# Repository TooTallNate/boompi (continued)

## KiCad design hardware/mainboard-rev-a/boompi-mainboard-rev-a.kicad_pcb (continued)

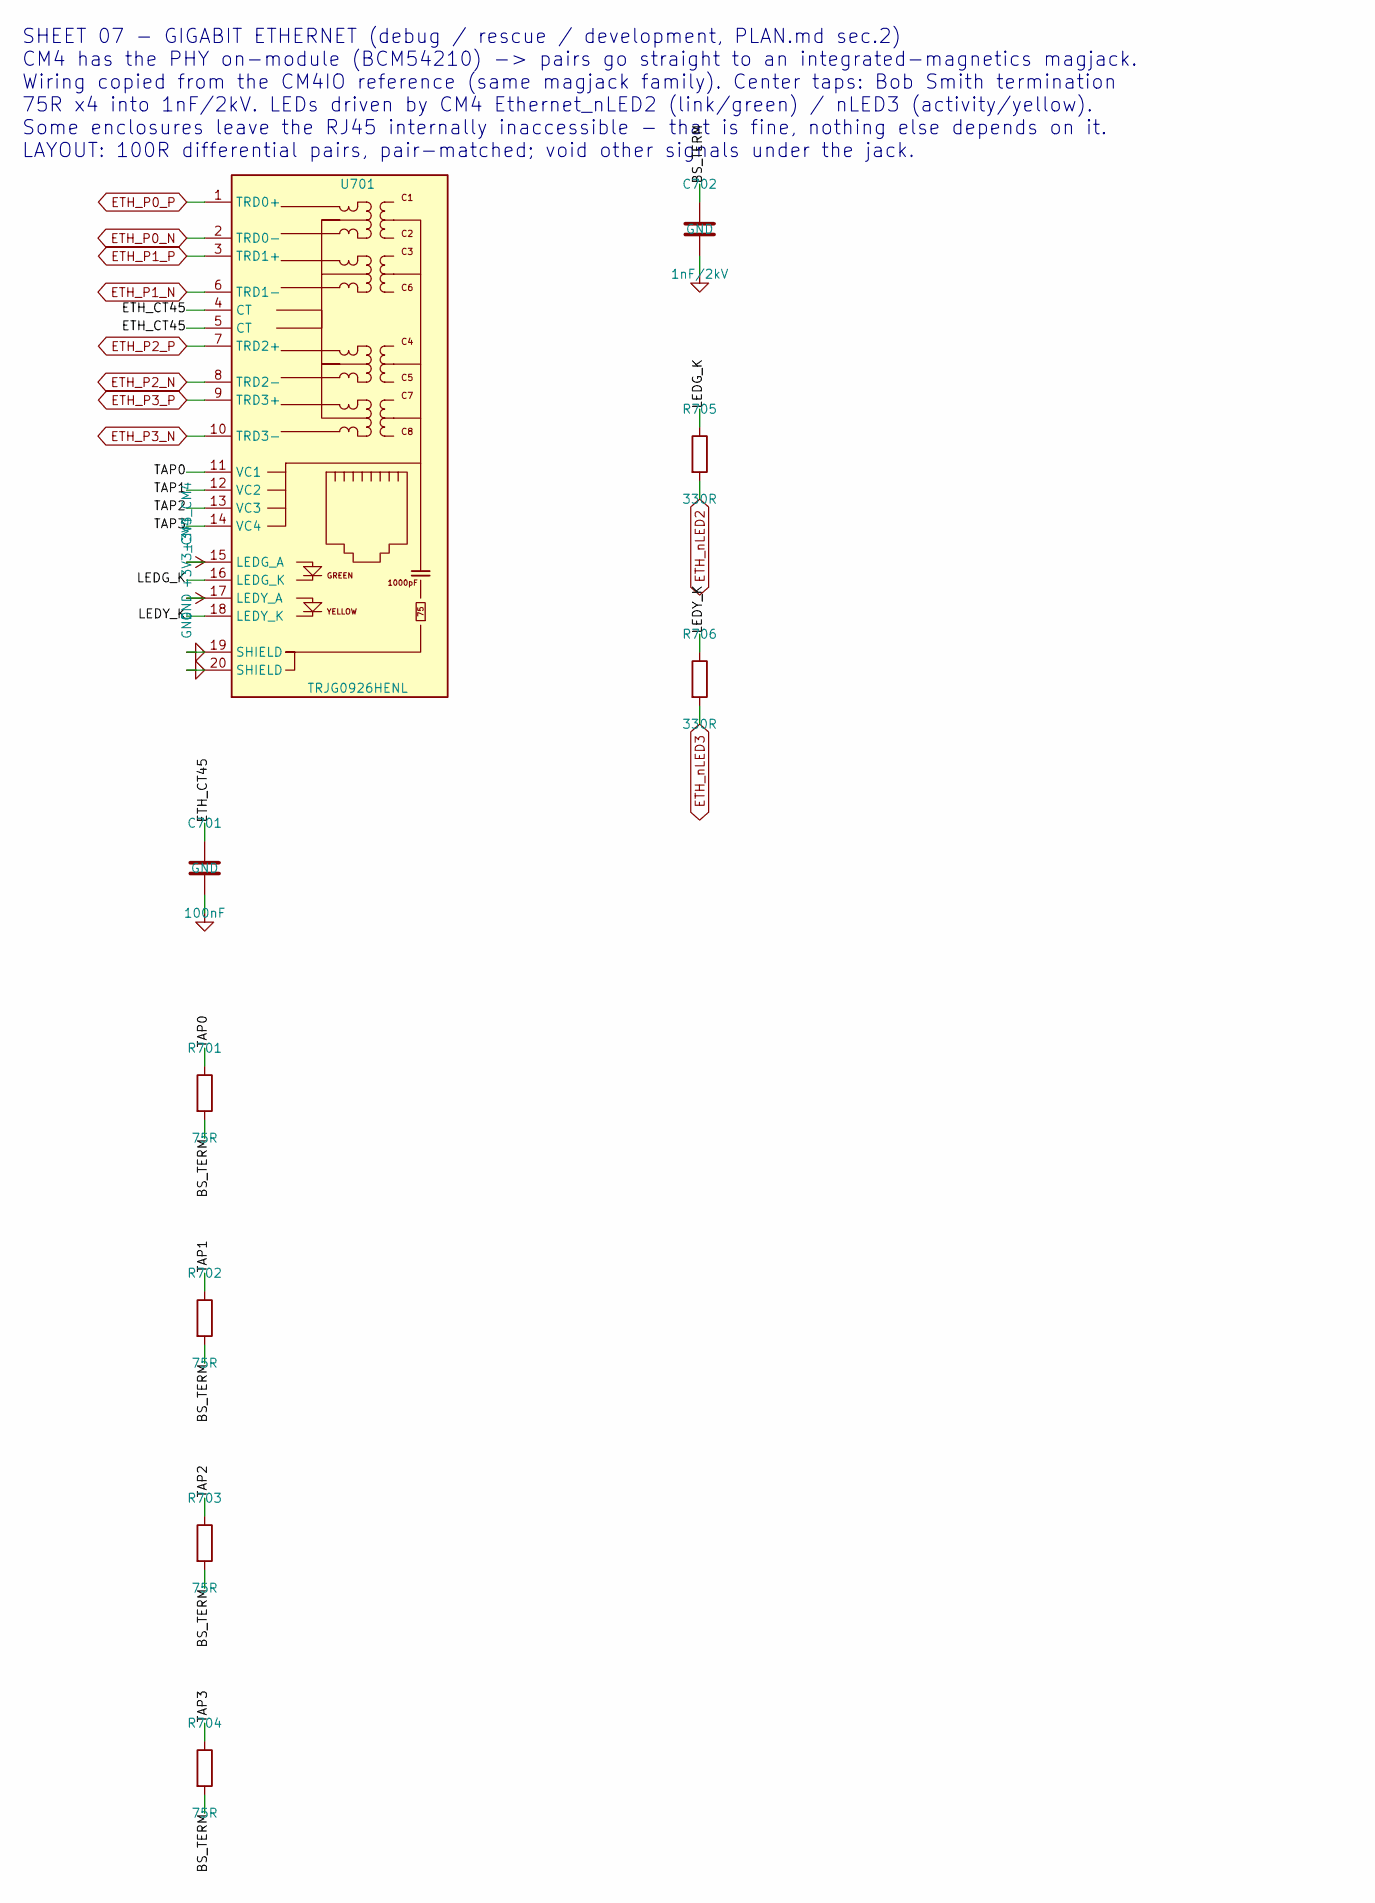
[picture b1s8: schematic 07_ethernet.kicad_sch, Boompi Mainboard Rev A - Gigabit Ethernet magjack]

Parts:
C701: 100nF; C_0603_1608Metric
C702: 1nF/2kV; C_1812_4532Metric
R701, R702, R703, R704: 75R; R_0603_1608Metric
R705, R706: 330R; R_0603_1608Metric
U701: TRJG0926HENL; MPN TRP TRJG0926HENL

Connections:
+3V3_CM4: U701.15 (LEDG_A), U701.17 (LEDY_A); also elsewhere on the board
/07_ETHERNET/BS_TERM: C702.1, R701.2, R702.2, R703.2, R704.2
/07_ETHERNET/ETH_CT45: C701.1, U701.4 (CT), U701.5 (CT)
/07_ETHERNET/LEDG_K: R705.1, U701.16 (LEDG_K)
/07_ETHERNET/LEDY_K: R706.1, U701.18 (LEDY_K)
/07_ETHERNET/TAP0: R701.1, U701.11 (VC1)
/07_ETHERNET/TAP1: R702.1, U701.12 (VC2)
/07_ETHERNET/TAP2: R703.1, U701.13 (VC3)
/07_ETHERNET/TAP3: R704.1, U701.14 (VC4)
ETH_P0_N: U701.2 (TRD0-); also elsewhere on the board
ETH_P0_P: U701.1 (TRD0+); also elsewhere on the board
ETH_P1_N: U701.6 (TRD1-); also elsewhere on the board
ETH_P1_P: U701.3 (TRD1+); also elsewhere on the board
ETH_P2_N: U701.8 (TRD2-); also elsewhere on the board
ETH_P2_P: U701.7 (TRD2+); also elsewhere on the board
ETH_P3_N: U701.10 (TRD3-); also elsewhere on the board
ETH_P3_P: U701.9 (TRD3+); also elsewhere on the board
ETH_nLED2: R705.2; also elsewhere on the board
ETH_nLED3: R706.2; also elsewhere on the board
GND: C701.2, C702.2, U701.19 (SHIELD), U701.20 (SHIELD); also elsewhere on the board

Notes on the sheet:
SHEET 07 - GIGABIT ETHERNET (debug / rescue / development, PLAN.md sec.2) CM4 has the PHY on-module (BCM54210) -> pairs go straight to an integrated-magnetics magjack. Wiring copied from the CM4IO reference (same magjack family). Center taps: Bob Smith termination 75R x4 into 1nF/2kV. LEDs driven b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

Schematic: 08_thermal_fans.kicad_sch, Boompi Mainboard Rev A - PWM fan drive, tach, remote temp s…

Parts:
J801: FAN1; PinHeader_1x04_P2.54mm_Vertical; MPN Molex 47053-1000 (4-pin fan)
J802: FAN2; PinHeader_1x04_P2.54mm_Vertical; MPN Molex 47053-1000 (4-pin fan)
J803: FAN3; PinHeader_1x04_P2.54mm_Vertical; MPN Molex 47053-1000 (4-pin fan); not fitted
J804: REMOTE_TEMP; JST_PH_B4B-PH-K_1x04_P2.00mm_Vertical; MPN JST B4B-PH-K-S
Q801, Q802: 2N7002; SOT-23
Q803: 2N7002; SOT-23; not fitted
R811, R821: 100R; R_0603_1608Metric
R812, R822: 100k; R_0603_1608Metric
R813, R814, R823, R824: 10k; R_0603_1608Metric
R815, R825: 1k; R_0603_1608Metric
R831: 100R; R_0603_1608Metric; not fitted
R832: 100k; R_0603_1608Metric; not fitted
R833, R834: 10k; R_0603_1608Metric; not fitted
R835: 1k; R_0603_1608Metric; not fitted

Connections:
+3V3_AON: J804.1, R814.1, R824.1, R834.1; also elsewhere on the board
+5V_MAIN: J801.2, J802.2, J803.2, R813.1, R823.1, R833.1; also elsewhere on the board
/08_THERMAL_FANS/FAN1_G: Q801.1 (G), R811.2, R812.1
/08_THERMAL_FANS/FAN1_PWM: J801.4, Q801.3 (D), R813.2
/08_THERMAL_FANS/FAN1_T_RAW: J801.3, R814.2, R815.1
/08_THERMAL_FANS/FAN2_G: Q802.1 (G), R821.2, R822.1
/08_THERMAL_FANS/FAN2_PWM: J802.4, Q802.3 (D), R823.2
/08_THERMAL_FANS/FAN2_T_RAW: J802.3, R824.2, R825.1
/08_THERMAL_FANS/FAN3_G: Q803.1 (G), R831.2, R832.1
/08_THERMAL_FANS/FAN3_PWM: J803.4, Q803.3 (D), R833.2
/08_THERMAL_FANS/FAN3_T_RAW: J803.3, R834.2, R835.1
FAN1_PWM_CTL: R811.1; also elsewhere on the board
FAN1_TACH: R815.2; also elsewhere on the board
FAN2_PWM_CTL: R821.1; also elsewhere on the board
FAN2_TACH: R825.2; also elsewhere on the board
FAN3_PWM_CTL: R831.1; also elsewhere on the board
FAN3_TACH: R835.2; also elsewhere on the board
GND: J801.1, J802.1, J803.1, J804.2, Q801.2 (S), Q802.2 (S), Q803.2 (S), R812.2, R822.2, R832.2; also elsewhere on the board
I2C_AON_SCL: J804.4; also elsewhere on the board
I2C_AON_SDA: J804.3; also elsewhere on the board

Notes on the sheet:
SHEET 08 - THERMAL / FANS (PLAN.md sec.6) Two populated 4-wire 5V PWM fan channels + optional third (FAN3 parts DNP). PWM: 2N7002 open-drain per Intel 4-wire fan spec (control input is pulled up INSIDE the fan; R8x3 is a board-side backup pull-up) - note the drive is INVERTING, handle in RP2040 fir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

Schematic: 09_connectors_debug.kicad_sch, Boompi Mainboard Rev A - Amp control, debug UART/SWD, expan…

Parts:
J901: AMP_MAIN_CTRL; JST_PH_B5B-PH-K_1x05_P2.00mm_Vertical; MPN JST B5B-PH-K-S
J902: AMP_SUB_CTRL; JST_PH_B4B-PH-K_1x04_P2.00mm_Vertical; MPN JST B4B-PH-K-S
J903: CM4_UART; PinHeader_1x03_P2.54mm_Vertical
J904: RP2040_UART; PinHeader_1x03_P2.54mm_Vertical
J905: I2C_EXP_CM4; JST_PH_B4B-PH-K_1x04_P2.00mm_Vertical; MPN JST B4B-PH-K-S
J906: SPI_EXP; PinHeader_1x08_P2.54mm_Vertical
J907: GPIO_EXP; PinHeader_1x10_P2.54mm_Vertical
R901, R904: 100k; R_0603_1608Metric
R902, R903, R905: 10k; R_0603_1608Metric
TP901: SYSTEM_BAT+; TestPoint_Pad_D1.5mm
TP902: +5V_MAIN; TestPoint_Pad_D1.5mm
TP903: +3V3_AON; TestPoint_Pad_D1.5mm
TP904: +3V3_CM4; TestPoint_Pad_D1.5mm
TP905, TP906: GND; TestPoint_Pad_D1.5mm
TP907: I2S_BCLK; TestPoint_Pad_D1.5mm
TP908: I2S_LRCLK; TestPoint_Pad_D1.5mm
TP909: I2S_DOUT; TestPoint_Pad_D1.5mm

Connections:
+3V3_AON: R902.1, R903.1, R905.1, TP903.1; also elsewhere on the board
+3V3_CM4: J905.1, J906.1, J907.1, TP904.1; also elsewhere on the board
+5V_MAIN: TP902.1; also elsewhere on the board
AMP_MAIN_EN: J901.1, R901.1; also elsewhere on the board
AMP_MAIN_FAULT: J901.2, R902.2; also elsewhere on the board
AMP_OTW: J901.3, R903.2; also elsewhere on the board
AMP_SUB_EN: J902.1, R904.1; also elsewhere on the board
AMP_SUB_FAULT: J902.2, R905.2; also elsewhere on the board
CM4_UART_RX: J903.2; also elsewhere on the board
CM4_UART_TX: J903.1; also elsewhere on the board
EXP_GPIO4: J907.3; also elsewhere on the board
EXP_GPIO5: J907.4; also elsewhere on the board
EXP_GPIO6: J907.5; also elsewhere on the board
EXP_GPIO12: J907.6; also elsewhere on the board
EXP_GPIO13: J907.7; also elsewhere on the board
EXP_GPIO16: J907.8; also elsewhere on the board
EXP_GPIO17: J907.9; also elsewhere on the board
EXP_GPIO20: J907.10; also elsewhere on the board
EXP_SPI_CE0: J906.6; also elsewhere on the board
EXP_SPI_CE1: J906.7; also elsewhere on the board
EXP_SPI_MISO: J906.4; also elsewhere on the board
EXP_SPI_MOSI: J906.3; also elsewhere on the board
EXP_SPI_SCLK: J906.5; also elsewhere on the board
GND: J901.4, J901.5, J902.3, J902.4, J903.3, J904.3, J905.2, J906.2, J906.8, J907.2, R901.2, R904.2, TP905.1, TP906.1; also elsewhere on the board
I2C_CM4_SCL: J905.4; also elsewhere on the board
I2C_CM4_SDA: J905.3; also elsewhere on the board
I2S_BCLK: TP907.1; also elsewhere on the board
I2S_DOUT: TP909.1; also elsewhere on the board
I2S_LRCLK: TP908.1; also elsewhere on the board
RP_UART_RX: J904.2; also elsewhere on the board
RP_UART_TX: J904.1; also elsewhere on the board
SYSTEM_BAT+: TP901.1; also elsewhere on the board

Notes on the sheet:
SHEET 09 - CONNECTORS / DEBUG (PLAN.md sec.7) Amp module control per PLAN.md amp-module requirement (EN + FAULT + OTW): J901 -> TPA3221 stereo module (EN default-off via R901; FAULT/OTW are open-drain, pulled to 3V3_AON). J902 -> TPA3221 PBTL subwoofer module. Amp POWER comes from J103/J104 on shee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

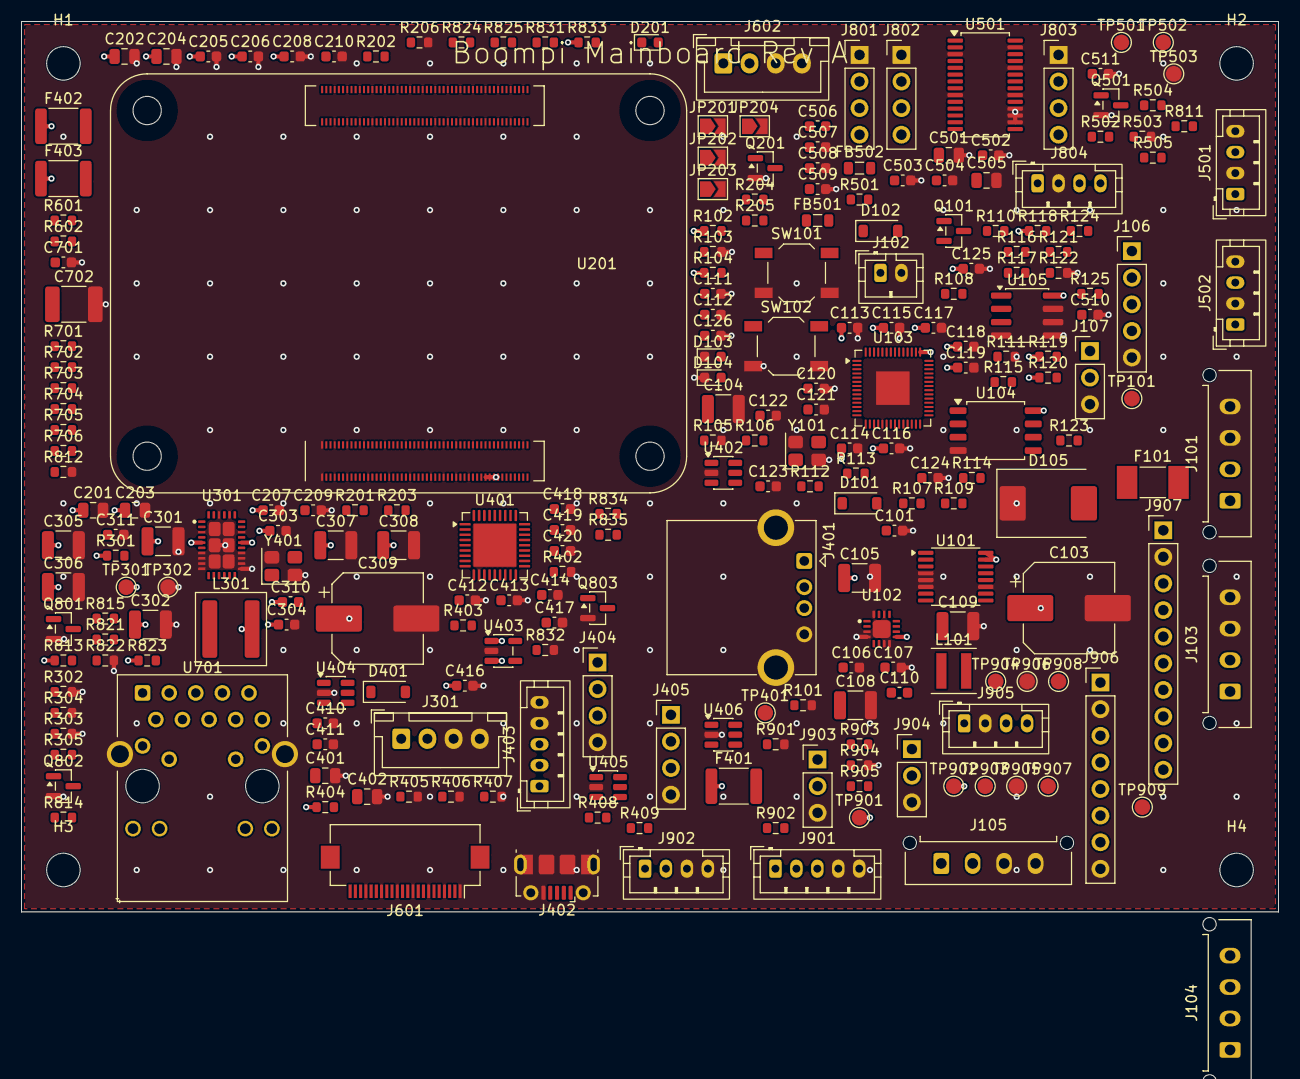
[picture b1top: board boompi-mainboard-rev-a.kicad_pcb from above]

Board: 6 copper layers, 120.0 x 85.0 mm, 240 parts (0 on the bottom side), 188 nets.

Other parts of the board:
H1, H2, H3, H4: MountingHole_3.2mm_M3

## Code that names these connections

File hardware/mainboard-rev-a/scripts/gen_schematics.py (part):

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        netmap={"1": VBAT, "2": l("BTN_GATE")})
s1.part("R109", S_R, value="1.5M", footprint=R0603,
        netmap={"1": l("BTN_GATE"), "2": l("PWR_BUTTON")})
s1.part("J102", S_CONN[2], value="PWR_BUTTON", footprint=PH2, mpn="JST B2B-PH-K-S",
        netmap={"1": l("PWR_BUTTON"), "2": GND})
s1.part("SW101", S_SW, value="PWR_BTN", footprint=SW_FP, mpn="E-Switch TL3342F160QG",
        netmap={"1": l("PWR_BUTTON"), "2": GND})
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        "current reads negative (PLAN.md sec.2). Reverse-polarity protection is by keyed connector + pack BMS.\n"
        "Power states: BTN press pulls PWR_BUTTON low -> Q101 drives AON_EN high -> LT8609S starts ->\n"
        "RP2040 boots and latches POWER_HOLD (via D101). STORAGE OFF = RP2040 drops POWER_HOLD.\n"
        "PWR_BTN_SENSE: ~2.9V idle, 0V pressed (GPIO18). VBAT_SENSE = SYSTEM_BAT+/11 (ADC0).\n"
        "I2C addresses: INA260=0x40, TMP1075=0x48 (remote sensor strap 0x49), RP2040 slave to CM4 on I2C_CM4.\n"
        "TVS D105 SMDJ26A: standoff 26V > 25.2V pack max; verify clamp < LT8609S 42V abs max at realistic surge.",
        30, 15, 2.0)
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    "15": g("ETH_nLED3"), "17": g("ETH_nLED2"),
    "20": l("EEPROM_WP_N"), "21": l("ACT_LED_K"),
    "24": g("CM4_SHUTDOWN_REQ"), "25": g("I2S_DOUT"), "26": g("I2S_LRCLK"),
    "27": g("EXP_GPIO20"), "28": g("EXP_GPIO13"), "29": g("EXP_GPIO16"),
    "30": g("EXP_GPIO6"), "31": g("EXP_GPIO12"), "34": g("EXP_GPIO5"),
    "37": g("EXP_SPI_CE1"), "38": g("EXP_SPI_SCLK"), "39": g("EXP_SPI_CE0"),
    "40": g("EXP_SPI_MISO"), "41": g("CM4_POWER_STATE"), "44": g("EXP_SPI_MOSI"),
    "49": g("I2S_BCLK"), "50": g("EXP_GPIO17"),
    "51": g("CM4_UART_RX"), "54": g("EXP_GPIO4"), "55": g("CM4_UART_TX"),
    "56": g("I2C_CM4_SCL"), "58": g("I2C_CM4_SDA"),
    "78": V3C, "80": g("DSI_SCL0"), "82": g("DSI_SDA0"),
    "89": l("WL_DIS"), "91": l("BT_DIS"), "92": g("CM4_RUN_PG"),
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s3.text("SHEET 03 - MAIN 5V RAIL (LT8645S Silent Switcher 2, per ADI datasheet fig.8)\n"
        "6S battery (max 25.2V) -> 5.15V nominal (R301/R302 = 1M/232k, VFB=0.97V) at up to 8A.\n"
        "fSW = 1MHz (RT=41.2k). SYNC/MODE=GND (Burst). INTVCC & BST caps are INTERNAL - pins float.\n"
        "Enable from RP2040 MAIN_5V_EN (GPIO6); R303 keeps rail OFF at power-up. PG -> GPIO25 via R305.\n"
        "Replaces the MP2307 UBEC that caused kernel undervoltage events (PLAN.md sec.2).\n"
        "LAYOUT: follow ADI demo board DC2874A - CIN tight to VIN/GND pins, small SW island, thermal vias under EP.",
        30, 15, 2.0)
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s5.flag_local("CPVDD_F")

s5.text("SHEET 05 - PCM5122 AUDIO DAC (PLAN.md sec.2)\n"
        "I2S from CM4 (GPIO18/19/21), control via I2C_CM4 @ 0x4C (ADR1=ADR2=0). MODE1/MODE2=0 -> I2C mode.\n"
        "SCK grounded: internal PLL generates the master clock from BCK (HiFiBerry-style, no external MCLK).\n"
        "2.0 VRMS ground-centered line out (VNEG charge pump) -> no output caps, no ground-loop isolator.\n"
        "XSMT: pulled up (unmuted) once 3V3_CM4 is up; RP2040 DAC_MUTE (GPIO29) can hard-mute via Q501\n"
        "during power transitions for pop-free sequencing (PLAN.md sec.5). J501 -> stereo amp module,\n"
        "J502 -> subwoofer amp module (module sums L+R).\n"
        "LAYOUT: keep this section away from LT8645S / USB / Ethernet / fan switching (PLAN.md sec.9).",
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                "5": g("EXP_SPI_SCLK"), "6": g("EXP_SPI_CE0"), "7": g("EXP_SPI_CE1"),
                "8": GND})
s9.part("J907", S_CONN[10], value="GPIO_EXP", footprint=HDR % 10,
        netmap={"1": V3C, "2": GND, "3": g("EXP_GPIO4"), "4": g("EXP_GPIO5"),
                "5": g("EXP_GPIO6"), "6": g("EXP_GPIO12"), "7": g("EXP_GPIO13"),
                "8": g("EXP_GPIO16"), "9": g("EXP_GPIO17"), "10": g("EXP_GPIO20")})
s9.part("TP901", S_TP, value="SYSTEM_BAT+", footprint=TP_FP, netmap={"1": VBAT})
s9.part("TP902", S_TP, value="+5V_MAIN", footprint=TP_FP, netmap={"1": V5})
s9.part("TP903", S_TP, value="+3V3_AON", footprint=TP_FP, netmap={"1": V3A})
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        "Amp module control per PLAN.md amp-module requirement (EN + FAULT + OTW):\n"
        "  J901 -> TPA3221 stereo module (EN default-off via R901; FAULT/OTW are open-drain, pulled to 3V3_AON).\n"
        "  J902 -> TPA3221 PBTL subwoofer module. Amp POWER comes from J103/J104 on sheet 01 (SYSTEM_BAT+).\n"
        "Debug: CM4 console UART (GPIO14/15), RP2040 console UART (GPIO0/1), RP2040 SWD on sheet 01 (J106).\n"
        "Expansion: CM4 SPI0 + 8 spare CM4 GPIOs + CM4 I2C. All 3V3 logic. Test points on every major rail.",
        30, 15, 2.0)

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
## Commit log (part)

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2020-12-14 Move click effect wrapper inside <main> and hide overflow
2020-12-14 Add hidden refresh mechanism by tapping bottom-right corner
2020-12-14 Hide the cursor
2020-12-14 Hide cursor on range input
2020-12-15 Remove cursor on battery chart
2020-12-15 Better battery charging styling
2020-12-15 Add click effect on "mousedown"
2020-12-15 Less debug
2020-12-15 More
2020-12-15 Better battery charge styling
2020-12-15 Show full charged
2020-12-15 Set battery read date on backend
2020-12-16 Send `uptime` upon WebSocket connection
2020-12-16 Make <ClickEffect> only remove the click divs after *all* effects have finished to prevent flicker effect
2020-12-16 Use localhost
2020-12-16 Transform <Header> into <Footer>
2020-12-16 Bigger font on connect bluetooth screen
2020-12-16 Add "Settings" icon
2020-12-16 Fix "is charged" logic
2020-12-16 Fix artificial play skip bug
2020-12-16 Better "now playing" styling
2020-12-16 Use `setTimeout()` instead of `requestAnimationFrame()`
    RAF is taking 50% CPU on the Pi 4.
2020-12-17 Add <Marquee> component
2020-12-17 Add left spacer and use `useLayoutEffect()`
2020-12-17 Fix build
2020-12-17 Fix styling on Chrome
2020-12-17 Fix "right" -> "to right"
2020-12-22 Remove <Settings> for now
2020-12-22 Fix <NowPlaying> label positioning
2020-12-22 Use "ease-in-out" easing function for <Marquee>
2021-01-03 Add `lib/utils.ts`
2021-01-03 Better amperage domain
2021-05-15 Use `@radix-ui/react-icons`
2021-05-15 Prettier
2021-05-15 Remove `mute` prop from <Volume> icon
2021-05-15 Use `@radix-ui/react-progress` for track position
2021-05-17 Use `@radix-ui/react-slider` for volume control
2022-05-29 Use `@tootallnate/ina260`
2022-05-30 Udpate to Next.js v12
2022-05-30 Make backend WebSocket URL configurable via env vars
2022-05-31 First pass at making styles be responsive to viewport width
2022-05-31 Remove "dbus-next" from frontend
2022-05-31 Add "private: true"
2022-05-31 Add "incremental: true"
2022-06-01 Add kiosk systemd service files
2022-06-01 Add `boompi.service` Next.js frontend systemd file
2022-06-01 Use better path to `kiosk.sh`
2022-06-01 Add `@types/i2c-bus` to root-level package.json
2022-06-19 Parse `PRETTY_HOSTNAME` from "/etc/machine-info" file
2022-08-01 Support `NEXT_PUBLIC_PRETTY_HOSTNAME` env var for local development
2022-08-01 Read `prettyHostname` from WebSocket connection
2022-08-01 Add "cava" subprocess
2022-08-02 `cava` doesn't like to write to "socket:" (a.k.a. "pipe" in Node.js), so use a FIFO instead
2022-08-02 mkfifo
2022-08-02 Use custom `cava` fork and use FD 3
2022-08-02 Send `ArrayBuffer` and only send proper page size
2022-08-02 Only broadcast if non-empty
2022-08-02 Add "pipe"
2022-08-02 Wait for more data
2022-08-02 Add framerate and fix page size calculation bug
2022-08-02 Prettier and only log broadcast message for non-binary
2022-08-04 Use flex in footer
2022-08-04 cava framerate 30
2022-08-06 Add cava to frontend WIP
2022-08-26 Add `create-battery-profile.ts`
2022-09-03 Use grey bars
